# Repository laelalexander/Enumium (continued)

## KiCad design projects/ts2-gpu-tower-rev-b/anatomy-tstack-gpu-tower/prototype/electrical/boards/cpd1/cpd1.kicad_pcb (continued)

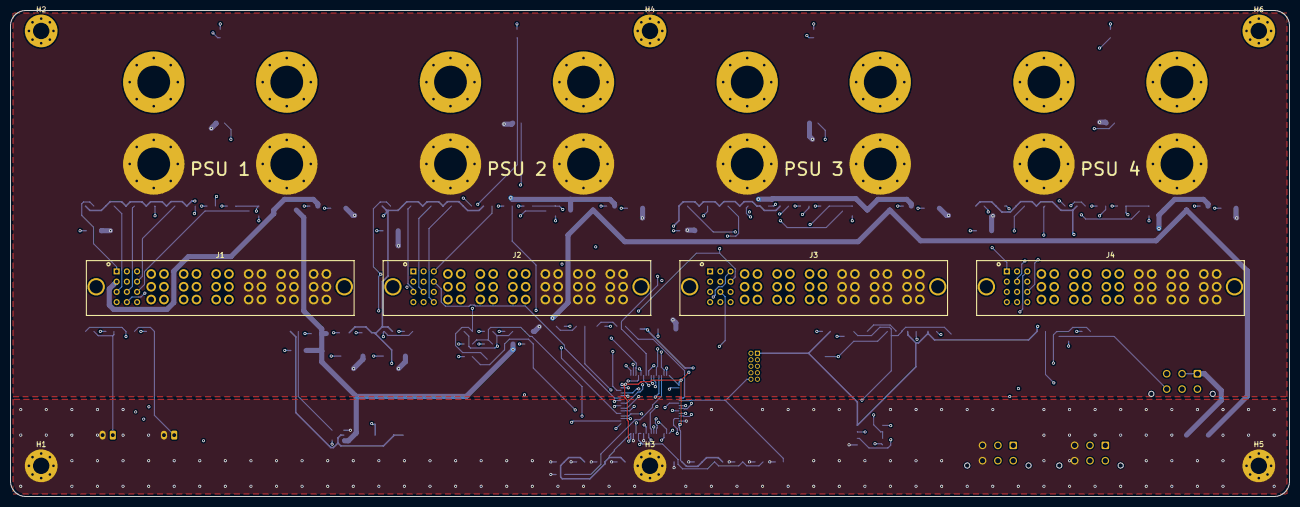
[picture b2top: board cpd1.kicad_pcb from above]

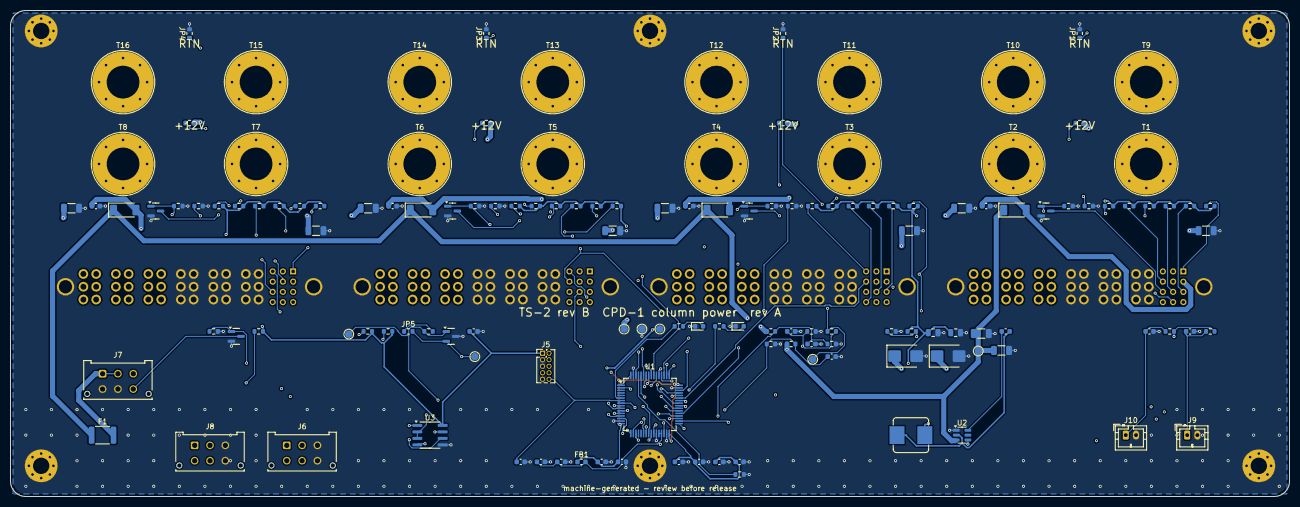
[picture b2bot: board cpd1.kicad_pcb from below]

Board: 6 copper layers, 250.0 x 95.0 mm, 150 parts (140 on the bottom side), 83 nets.

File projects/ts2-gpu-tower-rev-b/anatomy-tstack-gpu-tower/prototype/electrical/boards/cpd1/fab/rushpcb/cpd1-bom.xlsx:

CPD1 TS-2 rev B CPD-1 column power distribution rev A - Bill of Materials (qty 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
Item | Qty | Designators | Value | Description | Manufacturer | MPN | Supplier PN | Footprint | Side | DNP | Unit price USD (est.) | Ext. USD (est.)
1 | 14 | C1 C2 C3 C5 C50 C52 C53 C61 C62 C63 C64 C65 C68 C69 | 100n | MLCC 100 nF 50 V X7R 0603 | Samsung Electro-Mechanics | CL10B104KB8NNNC | LCSC C1591 | C_0603_1608Metric | Bottom |  | 0.01 | 0.14
2 | 2 | C4 C6 | 10u/50V | MLCC 10 uF 50 V X5R 1206 | Murata | GRM31CR61H106KA12L | LCSC C13585 | C_1206_3216Metric | Bottom |  | 0.06 | 0.12
3 | 2 | C7 C8 | 22u | MLCC 22 uF 25 V X5R 0805 | Samsung Electro-Mechanics | CL21A226MAQNNNE | LCSC C45783 | C_0805_2012Metric | Bottom |  | 0.06 | 0.12
4 | 1 | C66 | 4.7u | MLCC 4.7 uF 16 V X5R 0603 | Samsung Electro-Mechanics | CL10A475KO8NNNC | LCSC C19666 | C_0603_1608Metric | Bottom |  | 0.01 | 0.01
5 | 5 | C67 C101 C201 C301 C401 | 1u | VSB local | Samsung Electro-Mechanics | CL10A105KA8NNNC | LCSC C15849 | C_0603_1608Metric | Bottom |  | 0.01 | 0.05
6 | 8 | C102 C103 C202 C203 C302 C303 C402 C403 | 22u/25V | +12V HF decoupling at the blades | Samsung Electro-Mechanics | CL31A226KAHNNNE | LCSC C12891 | C_1206_3216Metric | Bottom |  | 0.06 | 0.48
7 | 4 | D1 D2 D3 D4 | PMEG4050EP | Schottky 40 V 5 A SOD-128, VSB OR-ing | Nexperia | PMEG4050EP,115 | 1727-4993-1-ND [verify] | D_SOD-128 | Bottom |  | 0.35 | 1.4
8 | 2 | D5 D6 | SMBJ15CA | TVS 15 V standoff 600 W bidirectional, +12V bus | Littelfuse | SMBJ15CA | SMBJ15CALFCT-ND [verify] | D_SMB | Bottom |  | 0.3 | 0.6
9 | 1 | D7 | SM712 | RS-485 TVS -7 / +12 V asymmetric | Semtech | SM712.TCT | SM712.TCTCT-ND [verify] | SOT-23 | Bottom |  | 0.4 | 0.4
10 | 1 | D8 | GREEN | LED green 0603 | Wurth Elektronik | 150060VS75000 | [verify] | LED_0603_1608Metric | Bottom |  | 0.15 | 0.15
11 | 1 | D9 | RED | LED red 0603 | Wurth Elektronik | 150060RS75000 | [verify] | LED_0603_1608Metric | Bottom |  | 0.15 | 0.15
12 | 1 | F1 | 2.5A | PTC 2.5 A hold 16 V 1812, standby feed to CCM-1 | Bourns | MF-MSMF250/16X-2 | MF-MSMF250/16X-2CT-ND [verify] | Fuse_1812_4532Metric | Bottom |  | 0.4 | 0.4
13 | 1 | FB1 | 600R | Ferrite 600 ohm @ 100 MHz, VDDA / VREF+ filter | Murata | BLM18KG601SN1D | 490-5258-1-ND [verify] | L_0603_1608Metric | Bottom |  | 0.1 | 0.1
14 | 4 | J1 J2 J3 J4 | CRPS PwrBlade | CRPS PSU mating receptacle, PwrBlade 6 power + 12 signal, vertical press-fit [v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 | Amphenol (FCI) | 10106264-6003003LF [verify] | [verify] | Amphenol_CRPS_PwrBlade_Vertical_PressFit | Top |  | 14 | 56
15 | 1 | J5 | SWD | Arm Cortex debug 10-pin 1.27 mm (SWD + SWO), keyed | Samtec | FTSH-105-01-F-DV-K | SAM8796-ND [verify] | PinHeader_2x05_P1.27mm_Vertical | Bottom |  | 2.1 | 2.1
16 | 3 | J6 J7 J8 | Micro-Fit 2x3 | Column RS-485 bus in/out: 1 A, 2 B, 3 GND, 4 ADDR0, 5 ADDR1, 6 GND (mating 4302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 | Molex | 43045-0612 | WM1784-ND [verify] | Molex_Micro-Fit_3.0_43045-0612_2x03_P3.00mm_Vertical | Bottom |  | 1.3 | 3.9
17 | 2 | J9 J10 | NTC | NTC 10k B3950 cable sensor: TS2B-232 strap (stud 4) | JST | B2B-PH-K-S | 455-1704-ND | JST_PH_B2B-PH-K_1x02_P2.00mm_Vertical | Bottom |  | 0.2 | 0.4
18 | 8 | JP1 JP2 JP3 JP4 R109 R209 R309 R409 | 0 | Remote sense + Kelvin link at the +12V stud | UNI-ROYAL | 0603WAF0000T5E | LCSC C21189 | R_0603_1608Metric | Bottom |  | 0.002 | 0.02
19 | 5 | JP5 R107 R207 R307 R407 | 0 | PMBus address strap - DNP (open = default address) | UNI-ROYAL | 0603WAF0000T5E | LCSC C21189 | R_0603_1608Metric | Bottom | DNP | 0.002 | 0
20 | 1 | L1 | 6.8u | Inductor 6.8 uH shielded 7.3 x 6.6 x 2.8 mm | Bourns | SRP7028A-6R8M | SRP7028A-6R8MCT-ND [verify] | L_Bourns_SRP7028A_7.3x6.6mm | Bottom |  | 0.6 | 0.6
21 | 5 | Q1 Q2 Q3 Q4 Q5 | 2N7002 | N-MOSFET 60 V 0.3 A SOT-23, PS_ON# driver | Nexperia | 2N7002,215 | 1727-2N7002215CT-ND | SOT-23 | Bottom |  | 0.05 | 0.25
22 | 9 | R1 R3 R5 R7 R14 R108 R208 R308 R408 | 100k | gate pull-down | UNI-ROYAL | 0603WAF1003T5E | LCSC C25803 | R_0603_1608Metric | Bottom |  | 0.002 | 0.02
23 | 1 | R2 | 33k | ISHARE divider bottom | UNI-ROYAL | 0603WAF3302T5E | LCSC C4216 | R_0603_1608Metric | Bottom |  | 0.002 | 0
24 | 3 | R4 R6 R8 | 22k | Resistor 22k 1% 0603 | UNI-ROYAL | 0603WAF2202T5E | LCSC C31850 | R_0603_1608Metric | Bottom |  | 0.002 | 0.01
25 | 1 | R10 | 120 | Bus termination 120 ohm - fit on the end node only | UNI-ROYAL | 0603WAF1200T5E | LCSC C22787 | R_0603_1608Metric | Bottom | DNP | 0.002 | 0
26 | 2 | R17 R18 | 1k | Resistor 1k 1% 0603 | UNI-ROYAL | 0603WAF1001T5E | LCSC C21190 | R_0603_1608Metric | Bottom |  | 0.002 | 0
27 | 22 | R9 R11 R12 R13 R15 R16 R101 R102 R103 R104 R201 R202 R203 R204 R301 R302 R303 R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 | 10k | PRESENT_L pull-up | UNI-ROYAL | 0603WAF1002T5E | LCSC C25804 | R_0603_1608Metric | Bottom |  | 0.002 | 0.04
28 | 8 | R105 R106 R205 R206 R305 R306 R405 R406 | 2.2k | PMBus SCL pull-up | UNI-ROYAL | 0603WAF2201T5E | LCSC C4190 | R_0603_1608Metric | Bottom |  | 0.002 | 0.02
29 | 16 | T1 T2 T3 T4 T5 T6 T7 T8 T9 T10 T11 T12 T13 T14 T15 T16 | M6 stud | M6 x 20 press-fit stud to the +12 V strap (B face), 12 mm pad all layers | PennEngineering | FHS-M6-20ZI [verify] | [verify] | Power_Stud_M6_PressFit | Bottom |  | 0.9 | 14.4
30 | 1 | U1 | STM32G474RET6 | MCU Arm Cortex-M4F 170 MHz, 512 KB flash, LQFP-64 (pin map from the KiCad STM32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 | STMicroelectronics | STM32G474RET6 | 497-19525-ND [verify] | LQFP-64_10x10mm_P0.5mm | Bottom |  | 7.9 | 7.9
31 | 1 | U2 | TPS54302 | Always-on 3.3 V buck from VSB_BUS | Texas Instruments | TPS54302DDCR | 296-47648-1-ND [verify] | SOT-23-6 | Bottom |  | 0.8 | 0.8
32 | 1 | U3 | THVD1420 | RS-485 half duplex 12 Mbps, 3.3 V, +/-12 kV ESD, fail-safe receiver | Texas Instruments | THVD1420DR | 296-THVD1420DRCT-ND [verify] | SOIC-8_3.9x4.9mm_P1.27mm | Bottom |  | 1.6 | 1.6
 |  |  |  | Estimated parts cost per board (excl. DNP, before price breaks) |  |  |  |  |  |  |  | 92.18000000000001

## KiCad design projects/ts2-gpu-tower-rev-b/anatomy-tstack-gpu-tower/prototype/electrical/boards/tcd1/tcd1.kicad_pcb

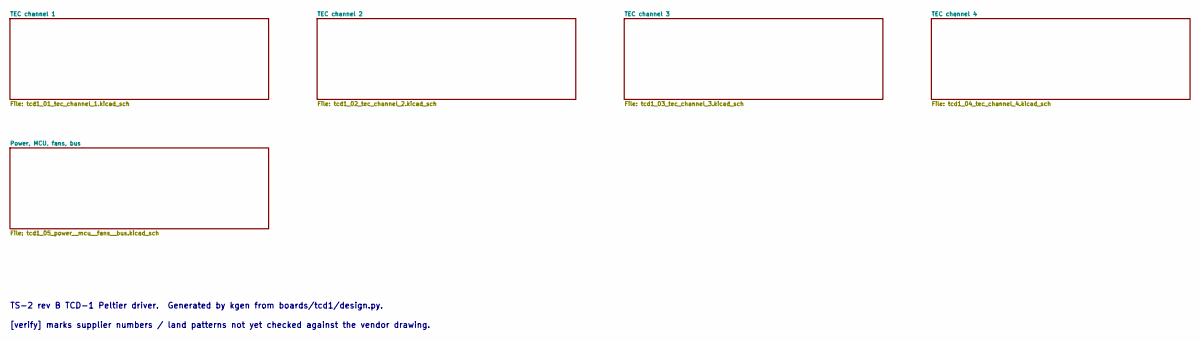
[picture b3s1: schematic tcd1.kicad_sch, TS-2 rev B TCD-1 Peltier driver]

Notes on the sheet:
TS-2 rev B TCD-1 Peltier driver. Generated by kgen from boards/tcd1/design.py.
[verify] marks supplier numbers / land patterns not yet checked against the vendor drawing.

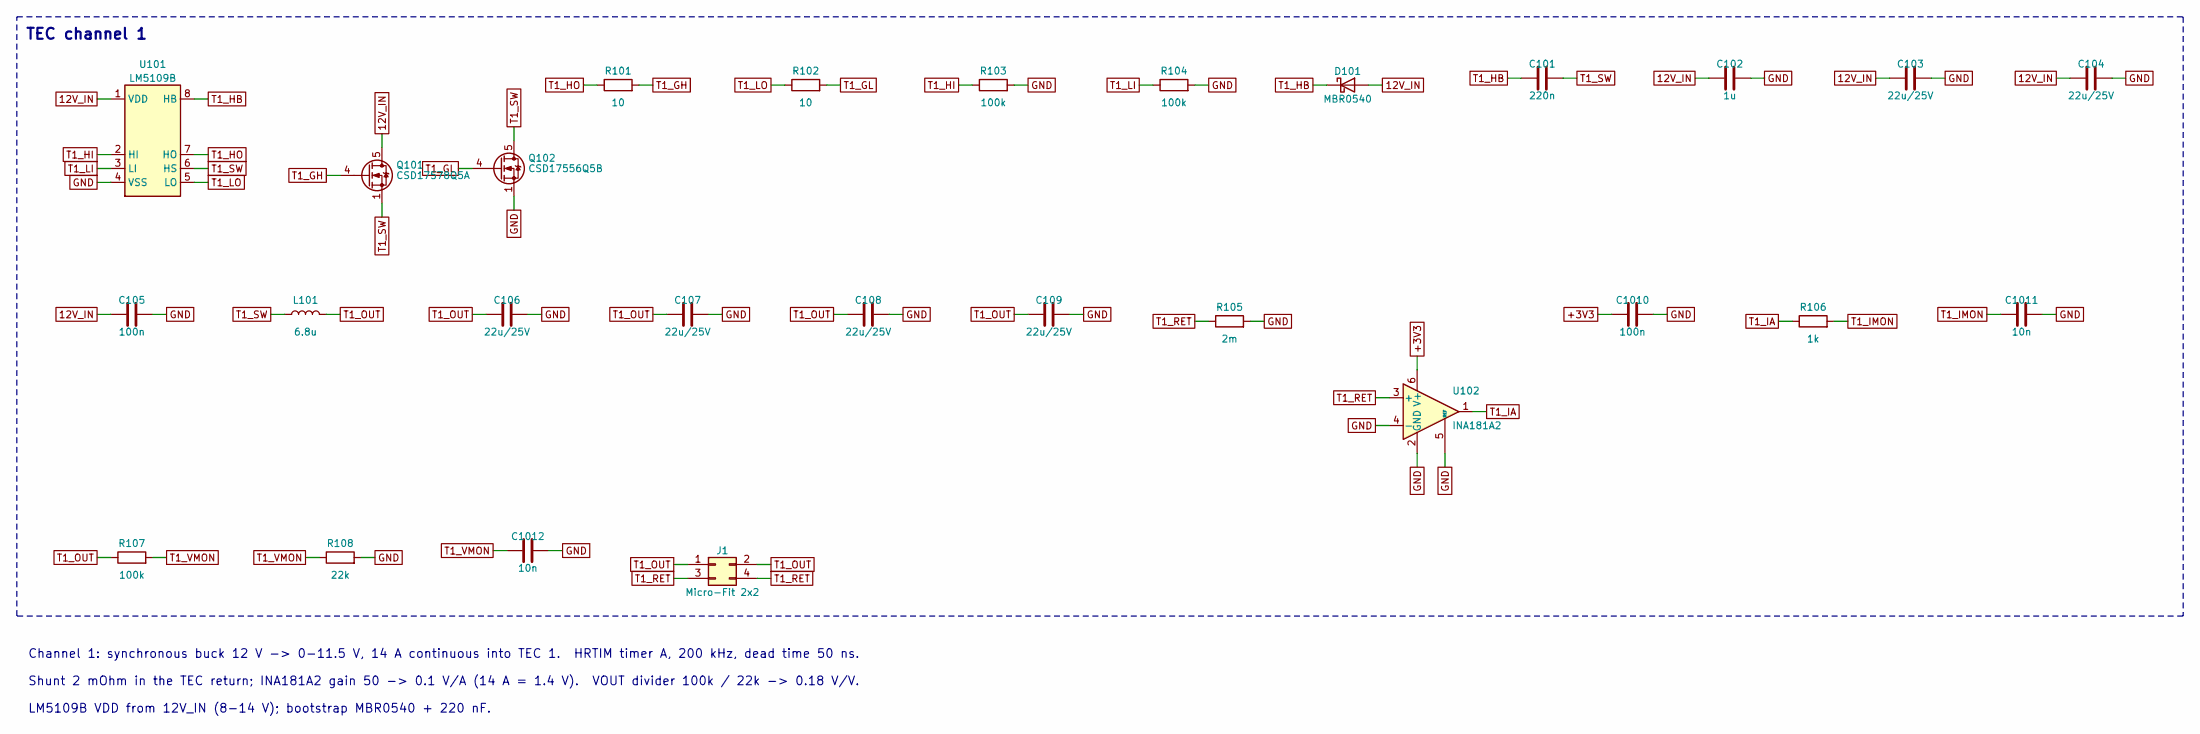
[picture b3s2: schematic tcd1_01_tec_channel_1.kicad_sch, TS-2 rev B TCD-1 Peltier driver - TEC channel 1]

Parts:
C101: 220n; C_0603_1608Metric; MPN CL10B224KO8NNNC; LCSC C21120
C102: 1u; C_0603_1608Metric; MPN CL10A105KA8NNNC; LCSC C15849
C103, C104, C106, C107, C108, C109: 22u/25V; C_1206_3216Metric; MPN CL31A226KAHNNNE; LCSC C12891
C105, C1010: 100n; C_0603_1608Metric; MPN CL10B104KB8NNNC; LCSC C1591
C1011, C1012: 10n; C_0603_1608Metric; MPN CL10B103KB8NNNC; LCSC C57112
D101: MBR0540; D_SOD-123; MPN MBR0540T1G
J1: Micro-Fit 2x2; Molex_Micro-Fit_3.0_43045-0412_2x02_P3.00mm_Vertical; MPN 43045-0412
L101: 6.8u; L_Vishay_IHLP-5050; MPN IHLP5050FDER6R8M01
Q101: CSD17578Q5A; TDSON-8-1; MPN CSD17578Q5A
Q102: CSD17556Q5B; TDSON-8-1; MPN CSD17556Q5B
R101, R102: 10; R_0603_1608Metric; MPN 0603WAF100JT5E; LCSC C22859
R103, R104, R107: 100k; R_0603_1608Metric; MPN 0603WAF1003T5E; LCSC C25803
R105: 2m; R_2512_6332Metric; MPN WSL2512R0020FEA
R106: 1k; R_0603_1608Metric; MPN 0603WAF1001T5E; LCSC C21190
R108: 22k; R_0603_1608Metric; MPN 0603WAF2202T5E; LCSC C31850
U101: LM5109B; SOIC-8_3.9x4.9mm_P1.27mm; MPN LM5109BMAX/NOPB
U102: INA181A2; SOT-23-6; MPN INA181A2IDBVR

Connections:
12V_IN: C102.1, C103.1, C104.1, C105.1, D101.2 (A), Q101.5 (D), U101.1 (VDD); also elsewhere on the board
+3V3: C1010.1, U102.6 (V+); also elsewhere on the board
GND: C102.2, C103.2, C104.2, C105.2, C106.2, C107.2, C108.2, C109.2, C1010.2, C1011.2, C1012.2, Q102.1 (S), Q102.2 (S), Q102.3 (S), R103.2, R104.2, R105.2, R108.2, U101.4 (VSS), U102.2 (GND), U102.4 (-), U102.5 (REF); also elsewhere on the board
T1_GH: Q101.4 (G), R101.2
T1_GL: Q102.4 (G), R102.2
T1_HB: C101.1, D101.1 (K), U101.8 (HB)
T1_HI: R103.1, U101.2 (HI); also elsewhere on the board
T1_HO: R101.1, U101.7 (HO)
T1_IA: R106.1, U102.1
T1_IMON: C1011.1, R106.2; also elsewhere on the board
T1_LI: R104.1, U101.3 (LI); also elsewhere on the board
T1_LO: R102.1, U101.5 (LO)
T1_OUT: C106.1, C107.1, C108.1, C109.1, J1.1, J1.2, L101.2, R107.1
T1_RET: J1.3, J1.4, R105.1, U102.3 (+)
T1_SW: C101.2, L101.1, Q101.1 (S), Q101.2 (S), Q101.3 (S), Q102.5 (D), U101.6 (HS)
T1_VMON: C1012.1, R107.2, R108.1; also elsewhere on the board

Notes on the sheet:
TEC channel 1
Channel 1: synchronous buck 12 V -> 0-11.5 V, 14 A continuous into TEC 1. HRTIM timer A, 200 kHz, dead time 50 ns.
Shunt 2 mOhm in the TEC return; INA181A2 gain 50 -> 0.1 V/A (14 A = 1.4 V). VOUT divider 100k / 22k -> 0.18 V/V.
LM5109B VDD from 12V_IN (8-14 V); bootstrap MBR0540 + 220 nF.

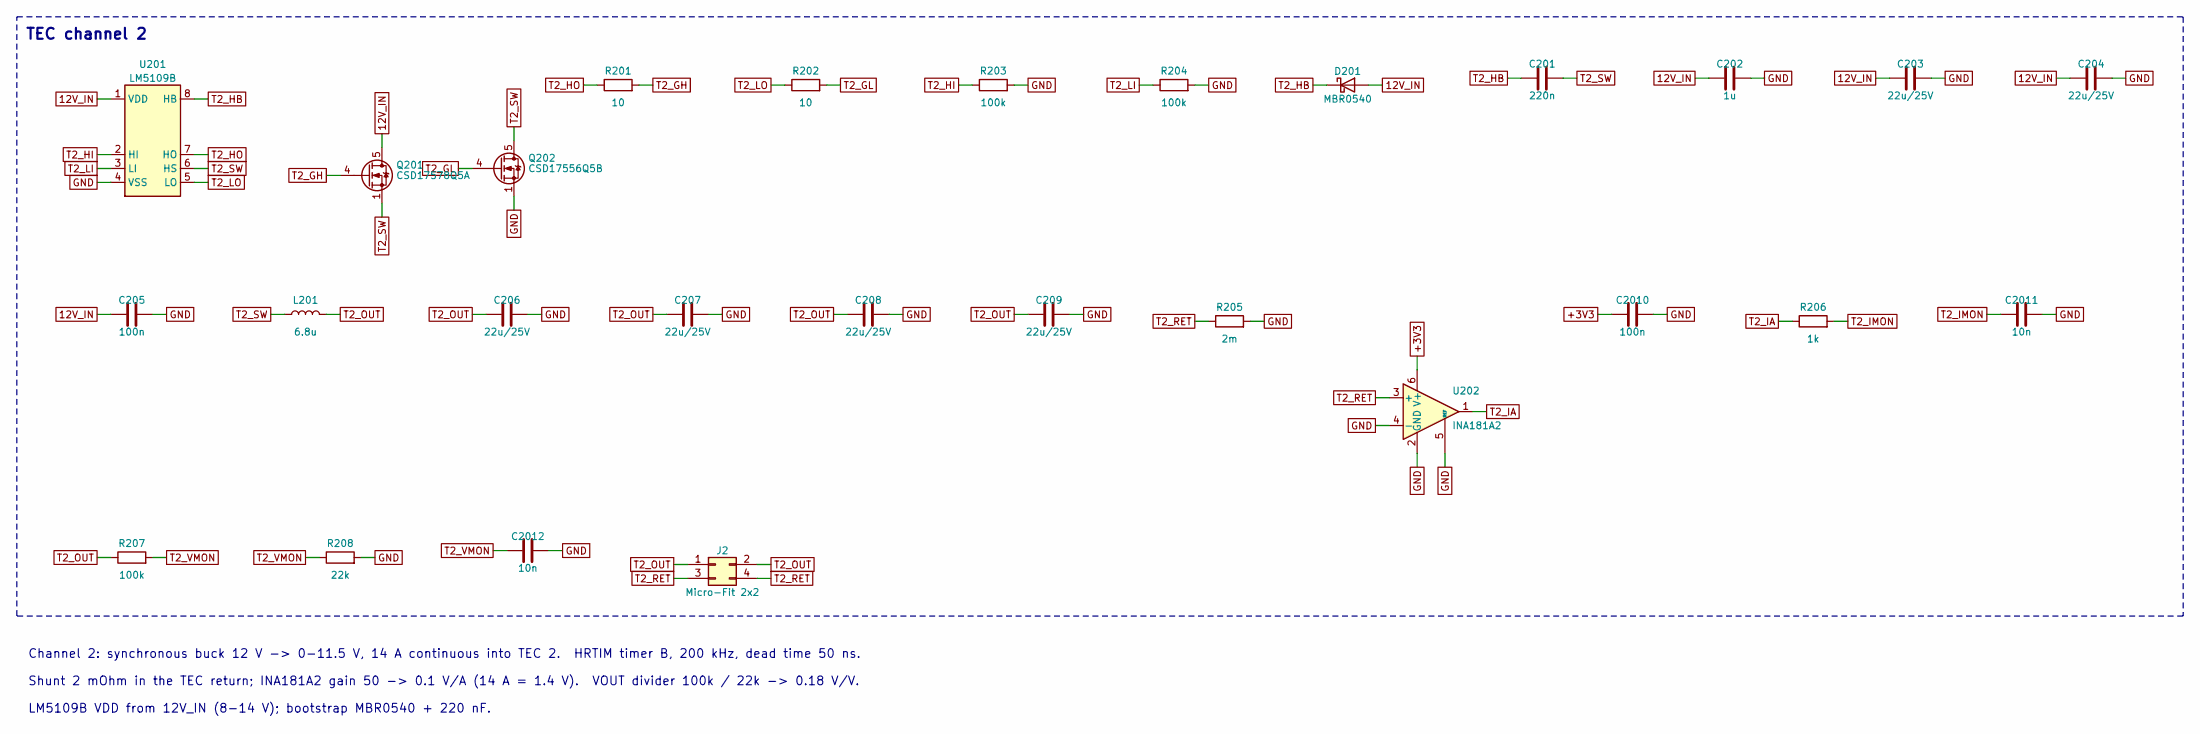
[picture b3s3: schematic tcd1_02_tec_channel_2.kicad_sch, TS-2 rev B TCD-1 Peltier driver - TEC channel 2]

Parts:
C201: 220n; C_0603_1608Metric; MPN CL10B224KO8NNNC; LCSC C21120
C202: 1u; C_0603_1608Metric; MPN CL10A105KA8NNNC; LCSC C15849
C203, C204, C206, C207, C208, C209: 22u/25V; C_1206_3216Metric; MPN CL31A226KAHNNNE; LCSC C12891
C205, C2010: 100n; C_0603_1608Metric; MPN CL10B104KB8NNNC; LCSC C1591
C2011, C2012: 10n; C_0603_1608Metric; MPN CL10B103KB8NNNC; LCSC C57112
D201: MBR0540; D_SOD-123; MPN MBR0540T1G
J2: Micro-Fit 2x2; Molex_Micro-Fit_3.0_43045-0412_2x02_P3.00mm_Vertical; MPN 43045-0412
L201: 6.8u; L_Vishay_IHLP-5050; MPN IHLP5050FDER6R8M01
Q201: CSD17578Q5A; TDSON-8-1; MPN CSD17578Q5A
Q202: CSD17556Q5B; TDSON-8-1; MPN CSD17556Q5B
R201, R202: 10; R_0603_1608Metric; MPN 0603WAF100JT5E; LCSC C22859
R203, R204, R207: 100k; R_0603_1608Metric; MPN 0603WAF1003T5E; LCSC C25803
R205: 2m; R_2512_6332Metric; MPN WSL2512R0020FEA
R206: 1k; R_0603_1608Metric; MPN 0603WAF1001T5E; LCSC C21190
R208: 22k; R_0603_1608Metric; MPN 0603WAF2202T5E; LCSC C31850
U201: LM5109B; SOIC-8_3.9x4.9mm_P1.27mm; MPN LM5109BMAX/NOPB
U202: INA181A2; SOT-23-6; MPN INA181A2IDBVR

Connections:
12V_IN: C202.1, C203.1, C204.1, C205.1, D201.2 (A), Q201.5 (D), U201.1 (VDD); also elsewhere on the board
+3V3: C2010.1, U202.6 (V+); also elsewhere on the board
GND: C202.2, C203.2, C204.2, C205.2, C206.2, C207.2, C208.2, C209.2, C2010.2, C2011.2, C2012.2, Q202.1 (S), Q202.2 (S), Q202.3 (S), R203.2, R204.2, R205.2, R208.2, U201.4 (VSS), U202.2 (GND), U202.4 (-), U202.5 (REF); also elsewhere on the board
T2_GH: Q201.4 (G), R201.2
T2_GL: Q202.4 (G), R202.2
T2_HB: C201.1, D201.1 (K), U201.8 (HB)
T2_HI: R203.1, U201.2 (HI); also elsewhere on the board
T2_HO: R201.1, U201.7 (HO)
T2_IA: R206.1, U202.1
T2_IMON: C2011.1, R206.2; also elsewhere on the board
T2_LI: R204.1, U201.3 (LI); also elsewhere on the board
T2_LO: R202.1, U201.5 (LO)
T2_OUT: C206.1, C207.1, C208.1, C209.1, J2.1, J2.2, L201.2, R207.1
T2_RET: J2.3, J2.4, R205.1, U202.3 (+)
T2_SW: C201.2, L201.1, Q201.1 (S), Q201.2 (S), Q201.3 (S), Q202.5 (D), U201.6 (HS)
T2_VMON: C2012.1, R207.2, R208.1; also elsewhere on the board

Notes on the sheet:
TEC channel 2
Channel 2: synchronous buck 12 V -> 0-11.5 V, 14 A continuous into TEC 2. HRTIM timer B, 200 kHz, dead time 50 ns.
Shunt 2 mOhm in the TEC return; INA181A2 gain 50 -> 0.1 V/A (14 A = 1.4 V). VOUT divider 100k / 22k -> 0.18 V/V.
LM5109B VDD from 12V_IN (8-14 V); bootstrap MBR0540 + 220 nF.

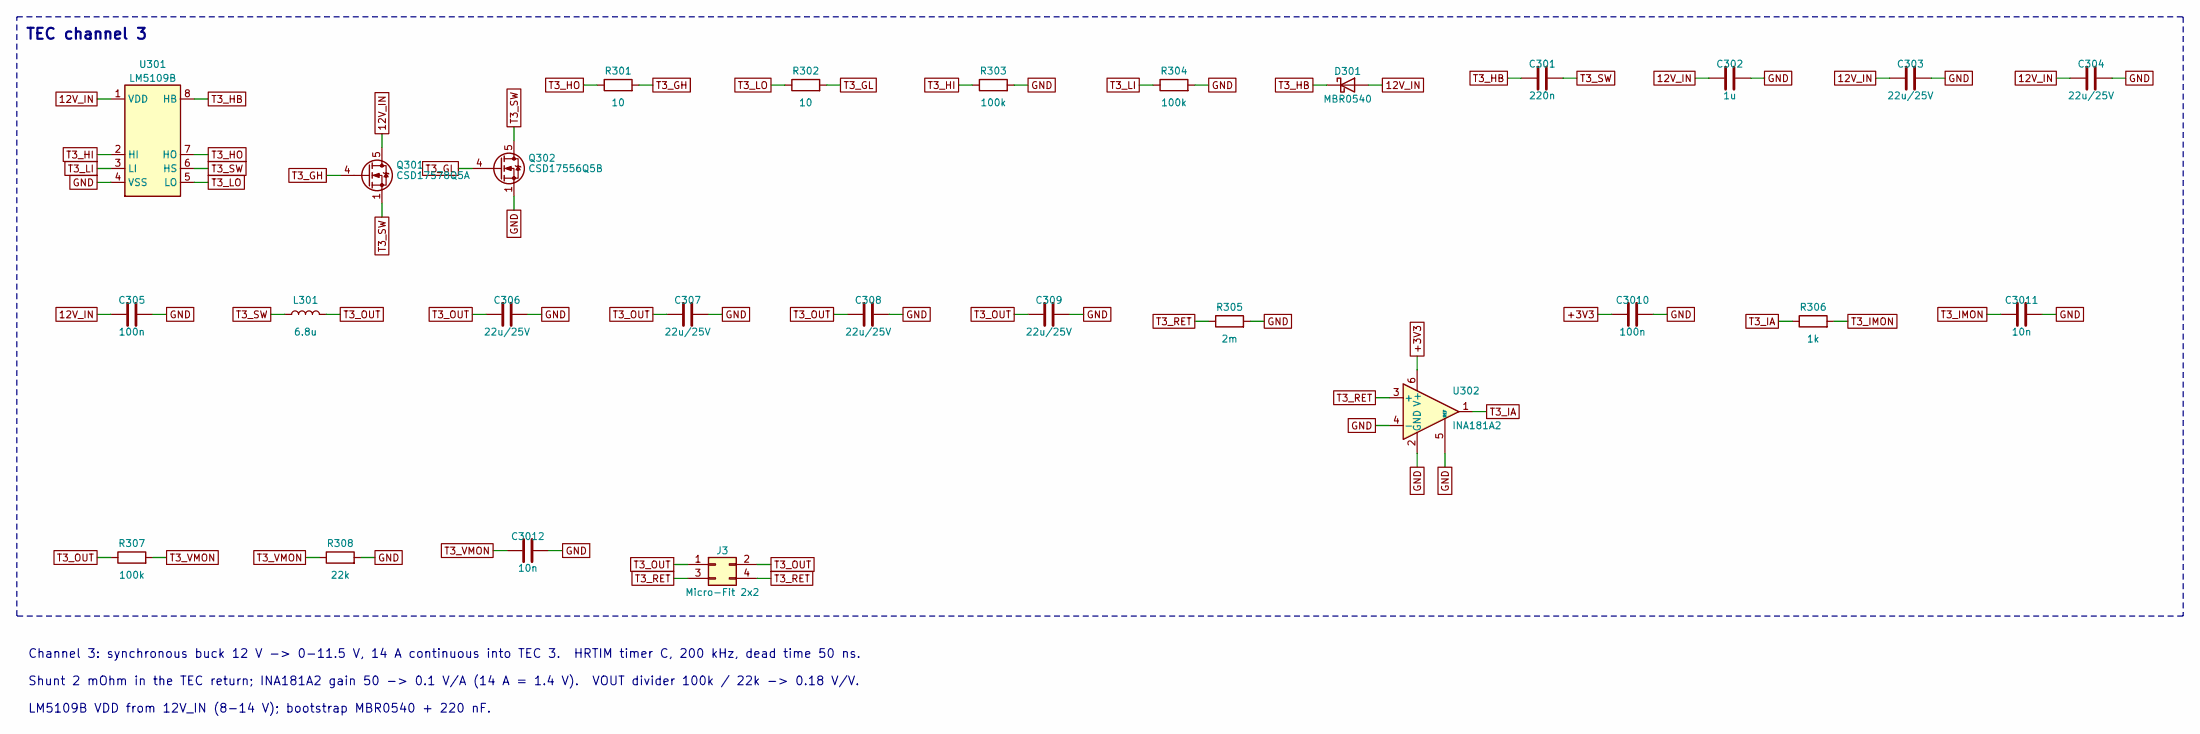
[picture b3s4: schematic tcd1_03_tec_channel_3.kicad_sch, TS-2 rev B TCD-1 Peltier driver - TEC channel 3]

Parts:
C301: 220n; C_0603_1608Metric; MPN CL10B224KO8NNNC; LCSC C21120
C302: 1u; C_0603_1608Metric; MPN CL10A105KA8NNNC; LCSC C15849
C303, C304, C306, C307, C308, C309: 22u/25V; C_1206_3216Metric; MPN CL31A226KAHNNNE; LCSC C12891
C305, C3010: 100n; C_0603_1608Metric; MPN CL10B104KB8NNNC; LCSC C1591
C3011, C3012: 10n; C_0603_1608Metric; MPN CL10B103KB8NNNC; LCSC C57112
D301: MBR0540; D_SOD-123; MPN MBR0540T1G
J3: Micro-Fit 2x2; Molex_Micro-Fit_3.0_43045-0412_2x02_P3.00mm_Vertical; MPN 43045-0412
L301: 6.8u; L_Vishay_IHLP-5050; MPN IHLP5050FDER6R8M01
Q301: CSD17578Q5A; TDSON-8-1; MPN CSD17578Q5A
Q302: CSD17556Q5B; TDSON-8-1; MPN CSD17556Q5B
R301, R302: 10; R_0603_1608Metric; MPN 0603WAF100JT5E; LCSC C22859
R303, R304, R307: 100k; R_0603_1608Metric; MPN 0603WAF1003T5E; LCSC C25803
R305: 2m; R_2512_6332Metric; MPN WSL2512R0020FEA
R306: 1k; R_0603_1608Metric; MPN 0603WAF1001T5E; LCSC C21190
R308: 22k; R_0603_1608Metric; MPN 0603WAF2202T5E; LCSC C31850
U301: LM5109B; SOIC-8_3.9x4.9mm_P1.27mm; MPN LM5109BMAX/NOPB
U302: INA181A2; SOT-23-6; MPN INA181A2IDBVR

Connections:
12V_IN: C302.1, C303.1, C304.1, C305.1, D301.2 (A), Q301.5 (D), U301.1 (VDD); also elsewhere on the board
+3V3: C3010.1, U302.6 (V+); also elsewhere on the board
GND: C302.2, C303.2, C304.2, C305.2, C306.2, C307.2, C308.2, C309.2, C3010.2, C3011.2, C3012.2, Q302.1 (S), Q302.2 (S), Q302.3 (S), R303.2, R304.2, R305.2, R308.2, U301.4 (VSS), U302.2 (GND), U302.4 (-), U302.5 (REF); also elsewhere on the board
T3_GH: Q301.4 (G), R301.2
T3_GL: Q302.4 (G), R302.2
T3_HB: C301.1, D301.1 (K), U301.8 (HB)
T3_HI: R303.1, U301.2 (HI); also elsewhere on the board
T3_HO: R301.1, U301.7 (HO)
T3_IA: R306.1, U302.1
T3_IMON: C3011.1, R306.2; also elsewhere on the board
T3_LI: R304.1, U301.3 (LI); also elsewhere on the board
T3_LO: R302.1, U301.5 (LO)
T3_OUT: C306.1, C307.1, C308.1, C309.1, J3.1, J3.2, L301.2, R307.1
T3_RET: J3.3, J3.4, R305.1, U302.3 (+)
T3_SW: C301.2, L301.1, Q301.1 (S), Q301.2 (S), Q301.3 (S), Q302.5 (D), U301.6 (HS)
T3_VMON: C3012.1, R307.2, R308.1; also elsewhere on the board

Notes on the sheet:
TEC channel 3
Channel 3: synchronous buck 12 V -> 0-11.5 V, 14 A continuous into TEC 3. HRTIM timer C, 200 kHz, dead time 50 ns.
Shunt 2 mOhm in the TEC return; INA181A2 gain 50 -> 0.1 V/A (14 A = 1.4 V). VOUT divider 100k / 22k -> 0.18 V/V.
LM5109B VDD from 12V_IN (8-14 V); bootstrap MBR0540 + 220 nF.

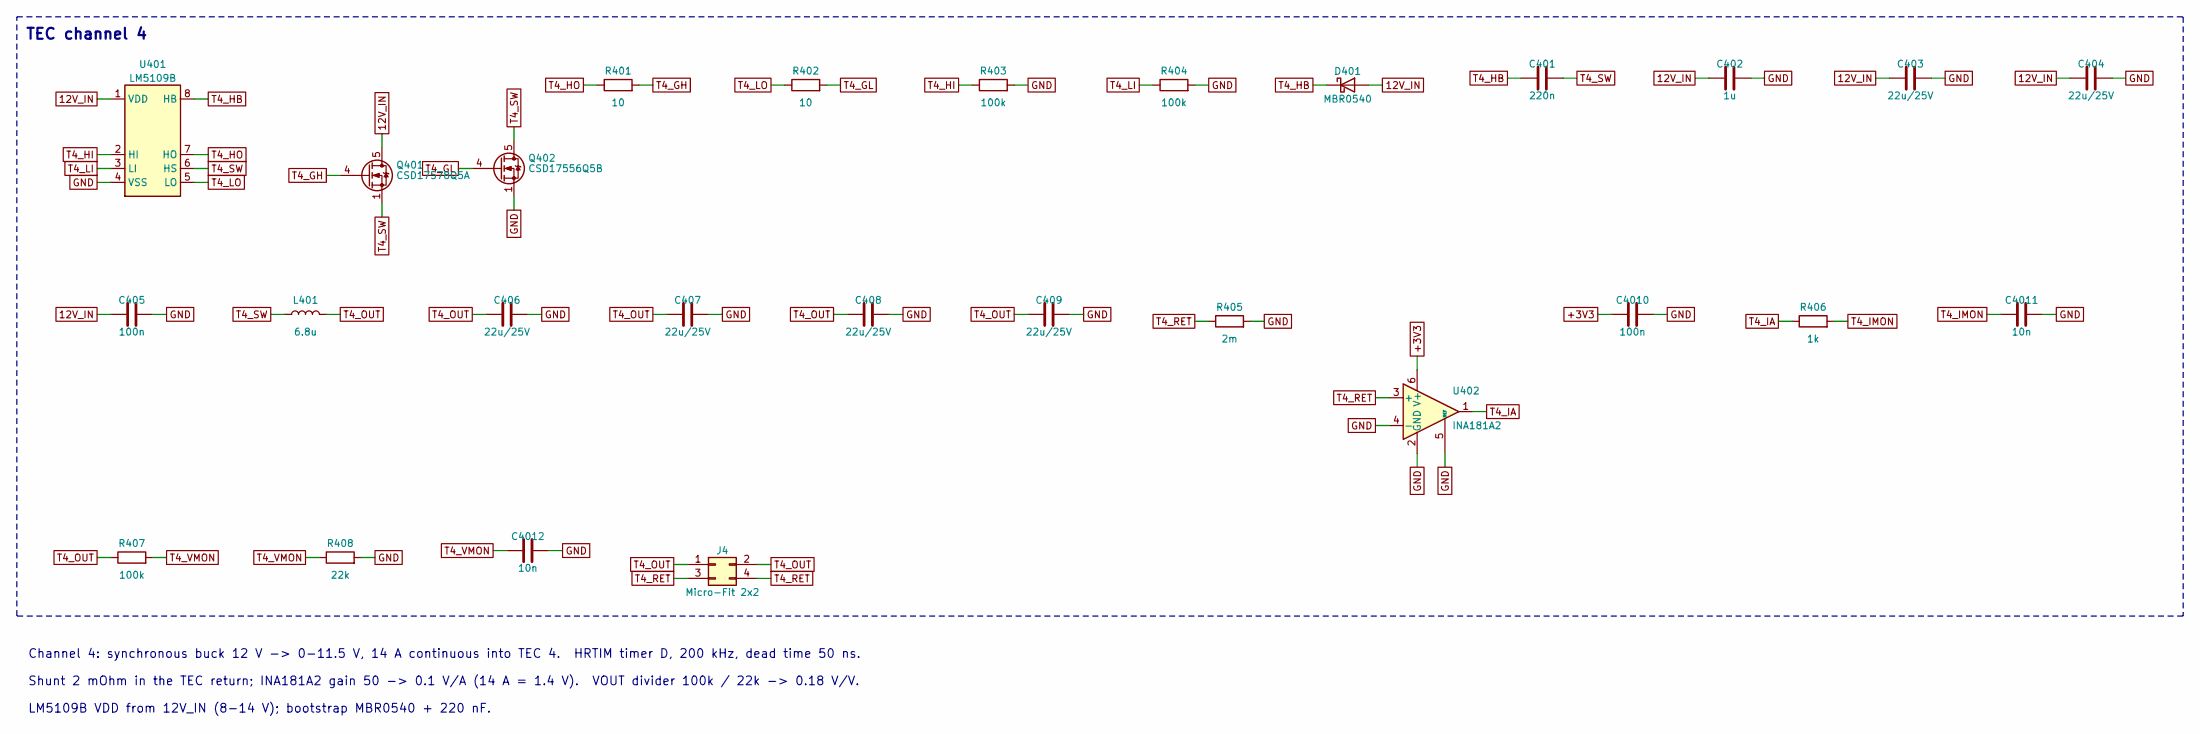
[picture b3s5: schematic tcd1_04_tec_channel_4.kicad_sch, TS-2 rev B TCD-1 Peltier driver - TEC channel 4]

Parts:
C401: 220n; C_0603_1608Metric; MPN CL10B224KO8NNNC; LCSC C21120
C402: 1u; C_0603_1608Metric; MPN CL10A105KA8NNNC; LCSC C15849
C403, C404, C406, C407, C408, C409: 22u/25V; C_1206_3216Metric; MPN CL31A226KAHNNNE; LCSC C12891
C405, C4010: 100n; C_0603_1608Metric; MPN CL10B104KB8NNNC; LCSC C1591
C4011, C4012: 10n; C_0603_1608Metric; MPN CL10B103KB8NNNC; LCSC C57112
D401: MBR0540; D_SOD-123; MPN MBR0540T1G
J4: Micro-Fit 2x2; Molex_Micro-Fit_3.0_43045-0412_2x02_P3.00mm_Vertical; MPN 43045-0412
L401: 6.8u; L_Vishay_IHLP-5050; MPN IHLP5050FDER6R8M01
Q401: CSD17578Q5A; TDSON-8-1; MPN CSD17578Q5A
Q402: CSD17556Q5B; TDSON-8-1; MPN CSD17556Q5B
R401, R402: 10; R_0603_1608Metric; MPN 0603WAF100JT5E; LCSC C22859
R403, R404, R407: 100k; R_0603_1608Metric; MPN 0603WAF1003T5E; LCSC C25803
R405: 2m; R_2512_6332Metric; MPN WSL2512R0020FEA
R406: 1k; R_0603_1608Metric; MPN 0603WAF1001T5E; LCSC C21190
R408: 22k; R_0603_1608Metric; MPN 0603WAF2202T5E; LCSC C31850
U401: LM5109B; SOIC-8_3.9x4.9mm_P1.27mm; MPN LM5109BMAX/NOPB
U402: INA181A2; SOT-23-6; MPN INA181A2IDBVR

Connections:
12V_IN: C402.1, C403.1, C404.1, C405.1, D401.2 (A), Q401.5 (D), U401.1 (VDD); also elsewhere on the board
+3V3: C4010.1, U402.6 (V+); also elsewhere on the board
GND: C402.2, C403.2, C404.2, C405.2, C406.2, C407.2, C408.2, C409.2, C4010.2, C4011.2, C4012.2, Q402.1 (S), Q402.2 (S), Q402.3 (S), R403.2, R404.2, R405.2, R408.2, U401.4 (VSS), U402.2 (GND), U402.4 (-), U402.5 (REF); also elsewhere on the board
T4_GH: Q401.4 (G), R401.2
T4_GL: Q402.4 (G), R402.2
T4_HB: C401.1, D401.1 (K), U401.8 (HB)
T4_HI: R403.1, U401.2 (HI); also elsewhere on the board
T4_HO: R401.1, U401.7 (HO)
T4_IA: R406.1, U402.1
T4_IMON: C4011.1, R406.2; also elsewhere on the board
T4_LI: R404.1, U401.3 (LI); also elsewhere on the board
T4_LO: R402.1, U401.5 (LO)
T4_OUT: C406.1, C407.1, C408.1, C409.1, J4.1, J4.2, L401.2, R407.1
T4_RET: J4.3, J4.4, R405.1, U402.3 (+)
T4_SW: C401.2, L401.1, Q401.1 (S), Q401.2 (S), Q401.3 (S), Q402.5 (D), U401.6 (HS)
T4_VMON: C4012.1, R407.2, R408.1; also elsewhere on the board

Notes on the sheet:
TEC channel 4
Channel 4: synchronous buck 12 V -> 0-11.5 V, 14 A continuous into TEC 4. HRTIM timer D, 200 kHz, dead time 50 ns.
Shunt 2 mOhm in the TEC return; INA181A2 gain 50 -> 0.1 V/A (14 A = 1.4 V). VOUT divider 100k / 22k -> 0.18 V/V.
LM5109B VDD from 12V_IN (8-14 V); bootstrap MBR0540 + 220 nF.
